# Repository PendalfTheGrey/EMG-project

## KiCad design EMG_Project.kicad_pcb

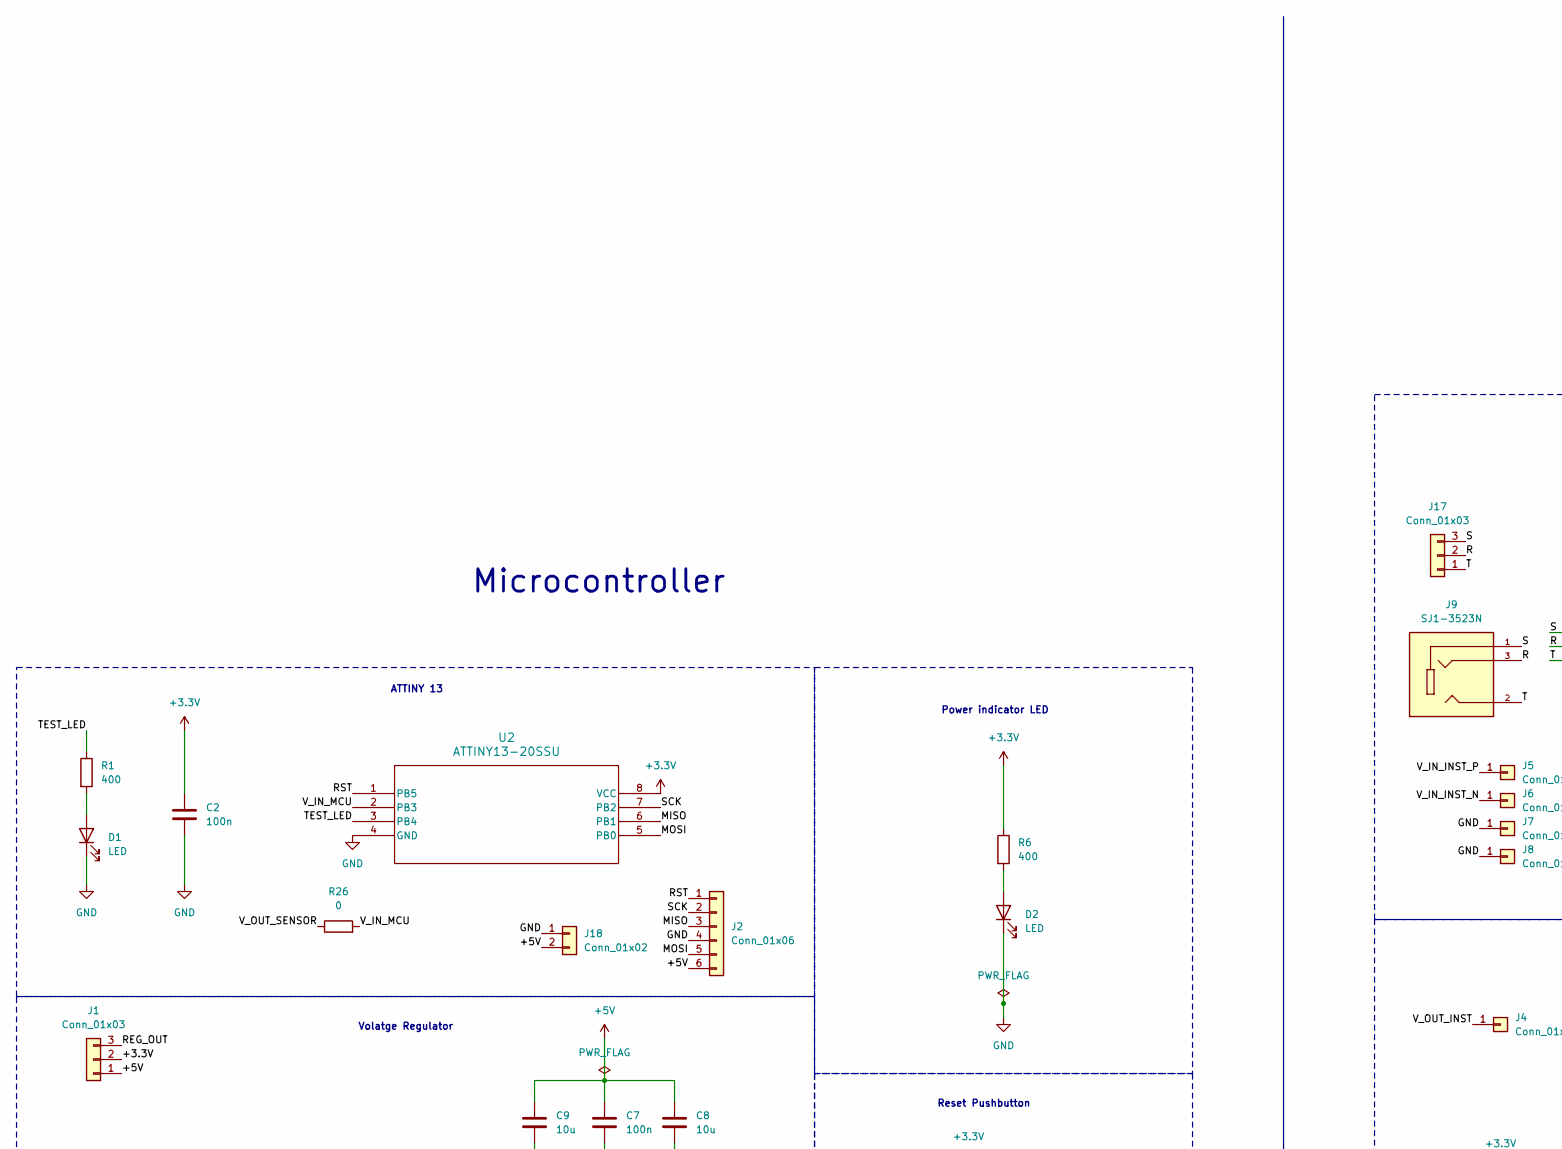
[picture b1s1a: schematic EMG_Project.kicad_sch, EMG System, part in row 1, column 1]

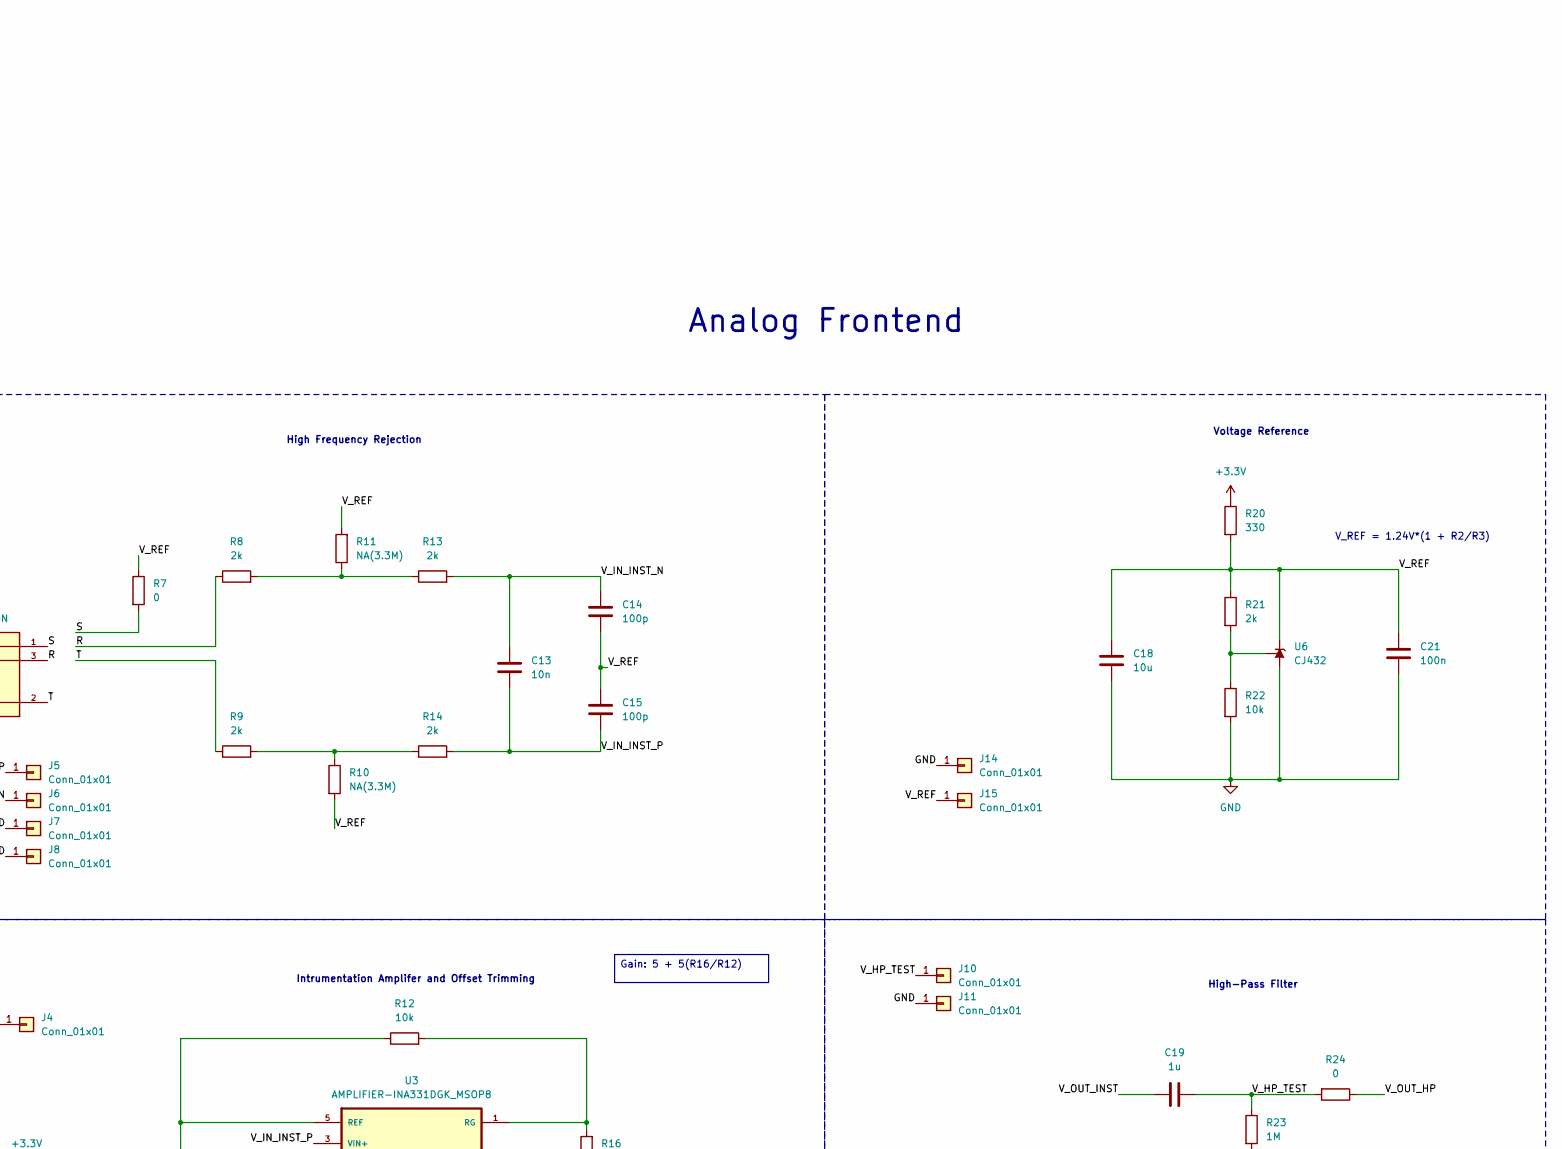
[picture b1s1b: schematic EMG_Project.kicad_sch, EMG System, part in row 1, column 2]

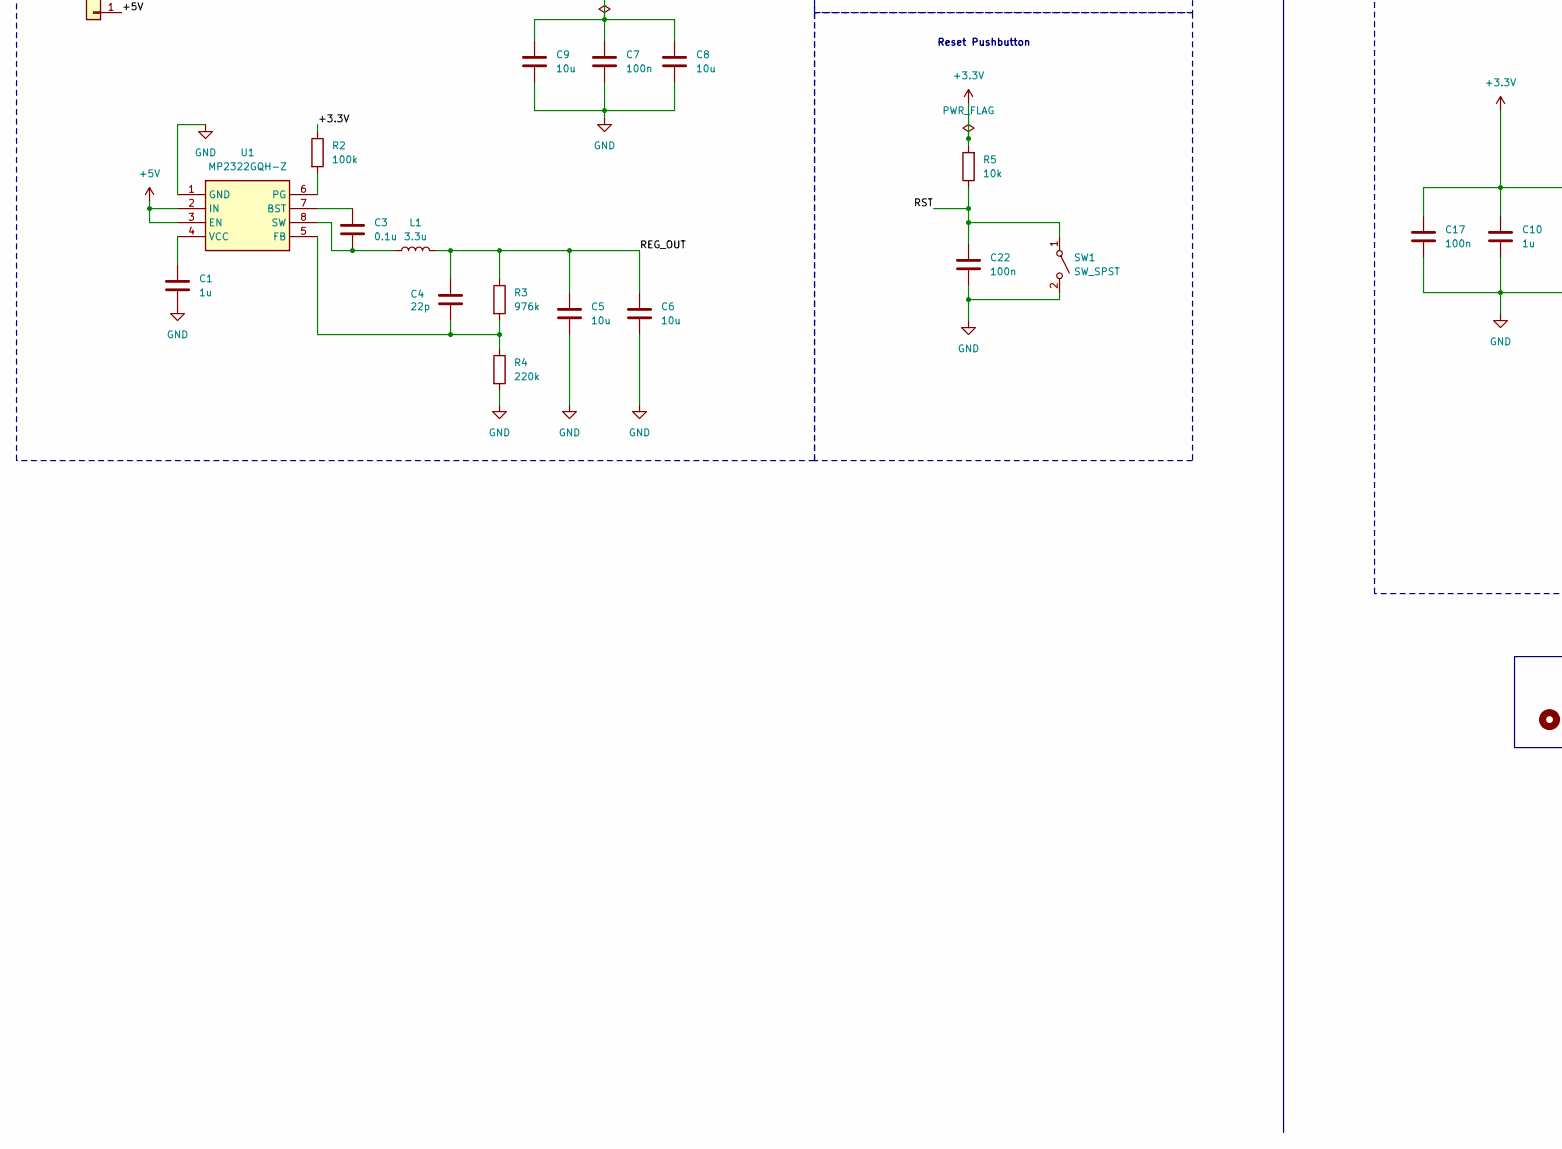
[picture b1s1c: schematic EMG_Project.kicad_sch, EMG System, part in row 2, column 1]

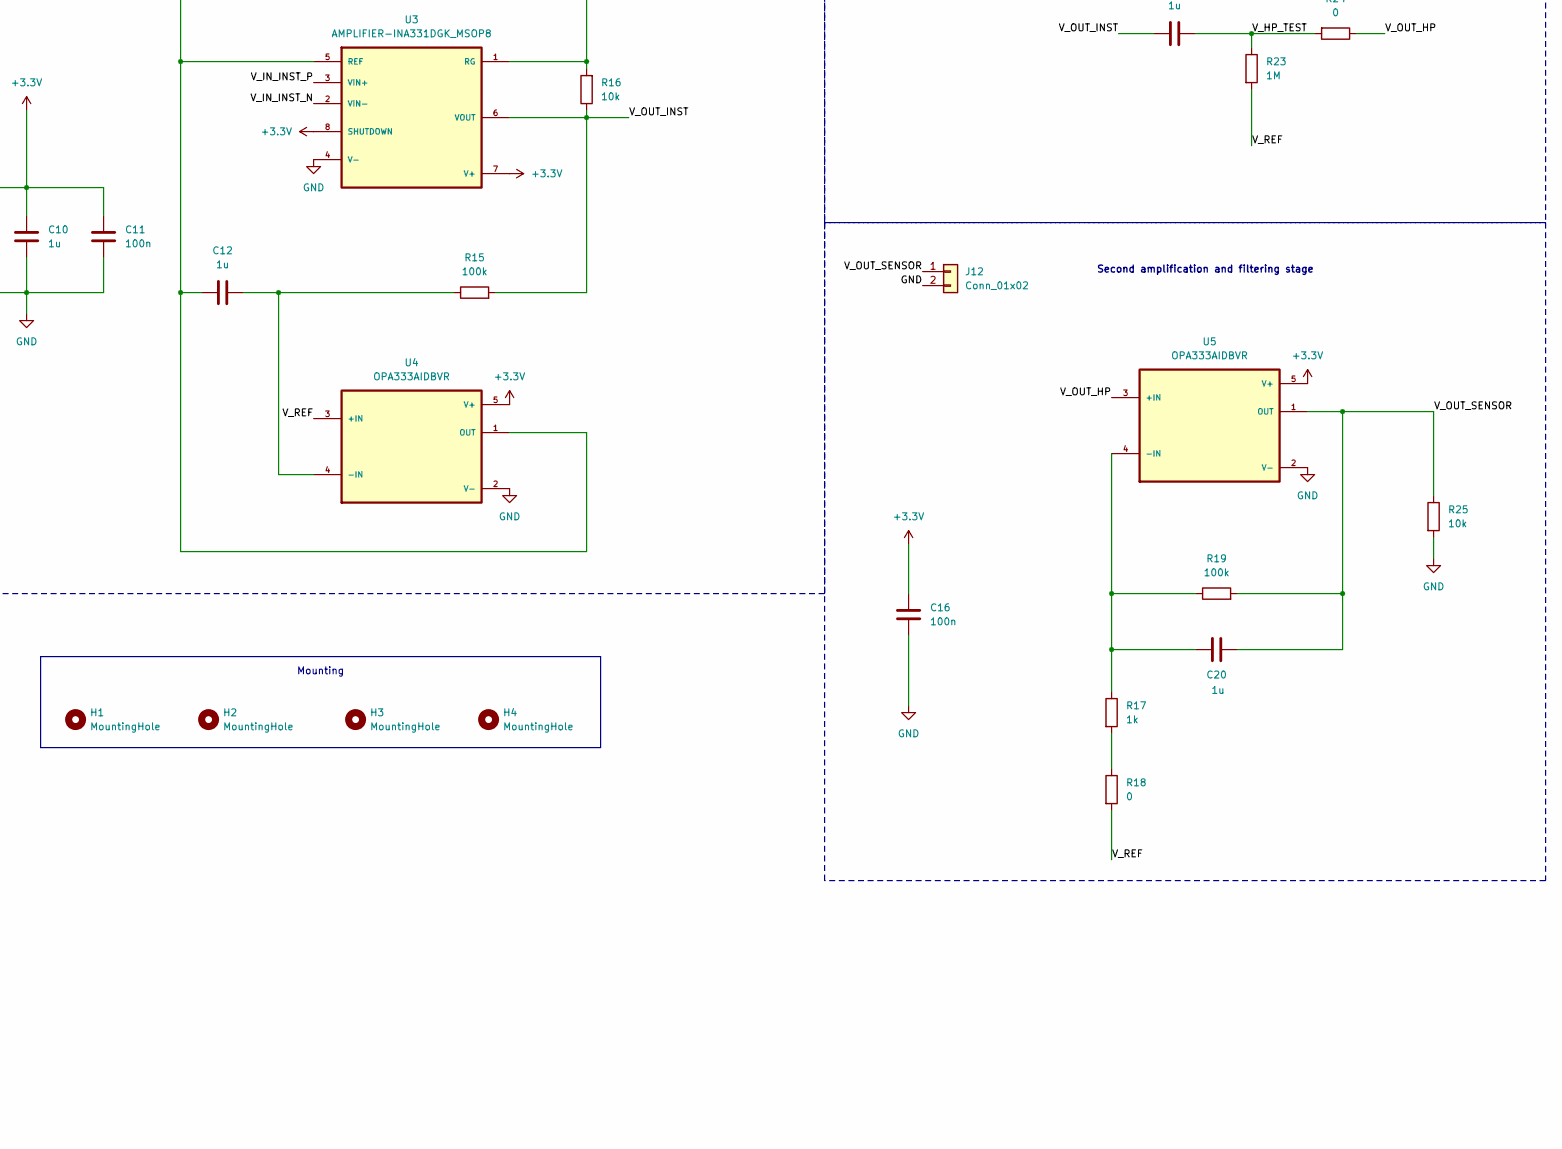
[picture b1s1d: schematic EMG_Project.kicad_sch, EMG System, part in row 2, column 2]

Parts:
C1, C10, C12, C19, C20: 1u; C_0603_1608Metric_Pad1.08x0.95mm_HandSolder
C2, C7, C11, C16, C17, C21, C22: 100n; C_0603_1608Metric_Pad1.08x0.95mm_HandSolder
C3: 0.1u; C_0603_1608Metric_Pad1.08x0.95mm_HandSolder
C4: 22p; C_0603_1608Metric_Pad1.08x0.95mm_HandSolder
C5, C6, C8, C9, C18: 10u; C_0603_1608Metric_Pad1.08x0.95mm_HandSolder
C13: 10n; C_0603_1608Metric_Pad1.08x0.95mm_HandSolder
C14, C15: 100p; C_0603_1608Metric_Pad1.08x0.95mm_HandSolder
D1, D2: LED; LED_0603_1608Metric_Pad1.05x0.95mm_HandSolder
H1, H2, H3, H4: MountingHole; MountingHole_3.2mm_M3_Pad
J1: Conn_01x03; PinHeader_1x03_P2.54mm_Vertical
J2: Conn_01x06; PinHeader_1x06_P2.54mm_Horizontal
J4, J5, J6, J7, J8, J10, J11, J14, J15: Conn_01x01; PinHeader_1x01_P2.54mm_Vertical
J9: SJ1-3523N; CUI_SJ1-3523N; PARTREV 1.05
J12, J18: Conn_01x02; PinHeader_1x02_P2.54mm_Horizontal
J17: Conn_01x03; PinHeader_1x03_P2.54mm_Horizontal
L1: 3.3u; L_0603_1608Metric_Pad1.05x0.95mm_HandSolder
R1, R6: 400; R_0603_1608Metric_Pad0.98x0.95mm_HandSolder
R2, R15, R19: 100k; R_0603_1608Metric_Pad0.98x0.95mm_HandSolder
R3: 976k; R_0603_1608Metric_Pad0.98x0.95mm_HandSolder
R4: 220k; R_0603_1608Metric_Pad0.98x0.95mm_HandSolder
R5, R12, R16, R22, R25: 10k; R_0603_1608Metric_Pad0.98x0.95mm_HandSolder
R7, R18, R24, R26: 0; R_0603_1608Metric_Pad0.98x0.95mm_HandSolder
R8, R9, R13, R14, R21: 2k; R_0603_1608Metric_Pad0.98x0.95mm_HandSolder
R10, R11: NA(3.3M); R_0603_1608Metric_Pad0.98x0.95mm_HandSolder
R17: 1k; R_0603_1608Metric_Pad0.98x0.95mm_HandSolder
R20: 330; R_0603_1608Metric_Pad0.98x0.95mm_HandSolder
R23: 1M; R_0603_1608Metric_Pad0.98x0.95mm_HandSolder
SW1: SW_SPST; SW_PUSH_6mm
U1: MP2322GQH-Z; QFN-8_1p5MMx2MM_MNP; Mouser Part Number 946-MP2322GQH-Z
U2: ATTINY13-20SSU; S8S1_ATM
U3: AMPLIFIER-INA331DGK_MSOP8; SOP65P490X110-8N
U4, U5: OPA333AIDBVR; SOT95P280X145-5N
U6: CJ432; SOT-23

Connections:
+3.3V: C2.1, C10.1, C11.1, C16.1, C17.1, J1.2, R2.1, R5.2, R6.1, R20.1, U2.8 (VCC), U3.7 (V+), U3.8 (SHUTDOWN), U4.5 (V+), U5.5 (V+)
+5V: C7.1, C8.1, C9.1, J1.1, J2.6, J18.2, U1.2 (IN), U1.3 (EN)
/MISO: J2.3, U2.6 (PB1)
/MOSI: J2.5, U2.5 (PB0)
/R: J9.3, J17.2, R8.1
/REG_OUT: C4.1, C5.1, C6.1, J1.3, L1.2, R3.1
/RST: C22.1, J2.1, R5.1, SW1.1 (A), U2.1 (PB5)
/S: J9.1, J17.3, R7.2
/SCK: J2.2, U2.7 (PB2)
/T: J9.2, J17.1, R9.1
/TEST_LED: R1.1, U2.3 (PB4)
/V_HP_TEST: C19.2, J10.1, R23.1, R24.2
/V_IN_INST_N: C13.1, C14.1, J6.1, R13.2, U3.2 (VIN-)
/V_IN_INST_P: C13.2, C15.2, J5.1, R14.2, U3.3 (VIN+)
/V_IN_MCU: R26.2, U2.2 (PB3)
/V_OUT_HP: R24.1, U5.3 (+IN)
/V_OUT_INST: C19.1, J4.1, R15.2, R16.1, U3.6 (VOUT)
/V_OUT_SENSOR: C20.1, J12.1, R19.2, R25.1, R26.1, U5.1 (OUT)
/V_REF: C14.2, C15.1, C18.1, C21.1, J15.1, R7.1, R10.2, R11.2, R18.2, R20.2, R21.1, R23.2, U4.3 (+IN), U6.2 (K)
GND: C1.2, C2.2, C5.2, C6.2, C7.2, C8.2, C9.2, C10.2, C11.2, C16.2, C17.2, C18.2, C21.2, C22.2, D1.1 (K), D2.1 (K), J2.4, J7.1, J8.1, J11.1, J12.2, J14.1, J18.1, R4.2, R22.2, R25.2, SW1.2 (B), U1.1 (GND), U2.4 (GND), U3.4 (V-), U4.2 (V-), U5.2 (V-), U6.3 (A)
unnamed: D1.2 (A), R1.2
unnamed: D2.2 (A), R6.2
unnamed: R9.2, R10.1, R14.1
unnamed: R8.2, R11.1, R13.1
unnamed: R17.2, R18.1
unnamed: C3.1, U1.7 (BST)
unnamed: C4.2, R3.2, R4.1, U1.5 (FB)
unnamed: R2.2, U1.6 (PG)
unnamed: C3.2, L1.1, U1.8 (SW)
unnamed: C1.1, U1.4 (VCC)
unnamed: C12.1, R12.1, U3.5 (REF), U4.1 (OUT)
unnamed: R12.2, R16.2, U3.1 (RG)
unnamed: C12.2, R15.1, U4.4 (-IN)
unnamed: C20.2, R17.1, R19.1, U5.4 (-IN)
unnamed: R21.2, R22.1, U6.1 (REF)

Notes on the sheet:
Second amplification and filtering stage
Intrumentation Amplifer and Offset Trimming
Volatge Regulator
V_REF = 1.24V*(1 + R2/R3)
Voltage Reference
High Frequency Rejection
Microcontroller
Reset Pushbutton
Analog Frontend
Mounting
ATTINY 13
High-Pass Filter
Power indicator LED
Gain: 5 + 5(R16/R12)

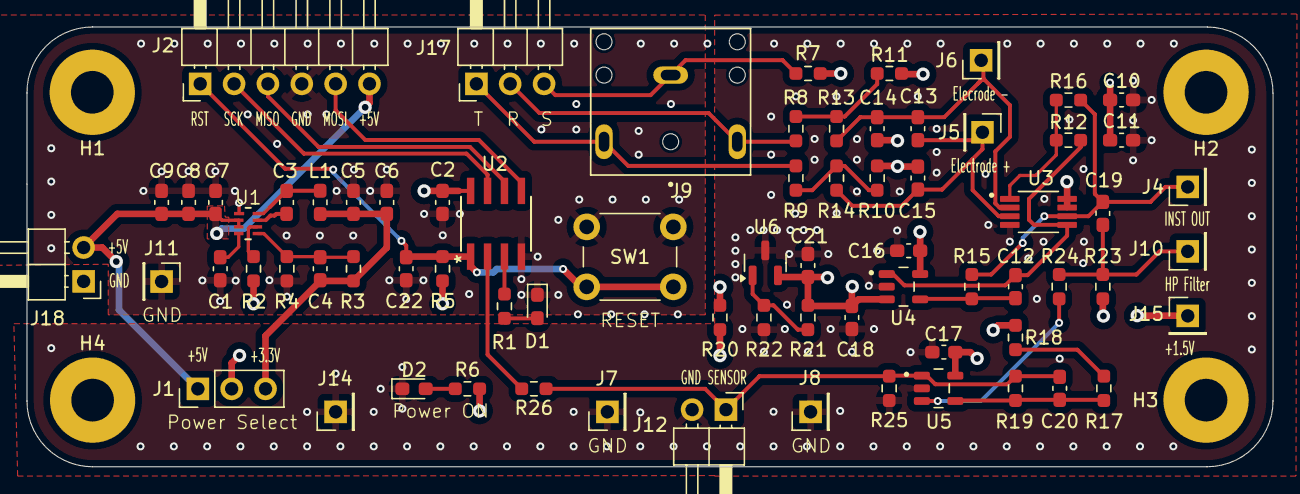
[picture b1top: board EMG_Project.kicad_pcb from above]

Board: 4 copper layers, 93.5 x 33.0 mm, 77 parts (0 on the bottom side), 35 nets.

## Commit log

2025-04-12 Updated gitignore
2025-04-12 Created project
2025-04-16 Added symbols for EMG sensor
2025-04-21 First version of the Sensor complete
2025-04-22 Added ATtiny
2025-04-23 Rearrangeed the footprints and symbols
2025-04-23 First version of the whole schematic
2025-04-24 Made Changes to the voltage regulator
2025-04-24 Assigned Footprints
2025-04-26 First layout sketch
2025-04-27 Everything prepared for routing
2025-04-27 Minor layout adjustments
2025-04-29 Routing of version 1 complete
2025-04-29 Minor grounding changes and gerber files
2025-05-20 Added BOM and minor fixes. Revision 1 complete
